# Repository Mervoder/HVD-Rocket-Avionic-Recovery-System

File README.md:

# HVD-Rocket-Avionic-Recovery-System
Rocket Main and Apogee Avionic Recovery System

1.5 ADANA WOF takımında takım arkadaşım MEHMET ALİ AĞIRMAN ile geliştirmiş olduğumuz Roket kurtarma sistemidir. 

Sistemde 2 adet açılma mevcuttur.

Kullanılan malzemeler :
MPU-6050
STM32F072
LoRa e32 433t30d
MS5611
Quectel L86 GPS

Tamamen örnek teşkil etmesi için yayımlanmıştır. İlgili kodlamalar ve detaylı bilgiler için iletişime geçebilirsiniz. 

OĞUZ KAAN ATAY
atay.oguzkaan@gmail.com

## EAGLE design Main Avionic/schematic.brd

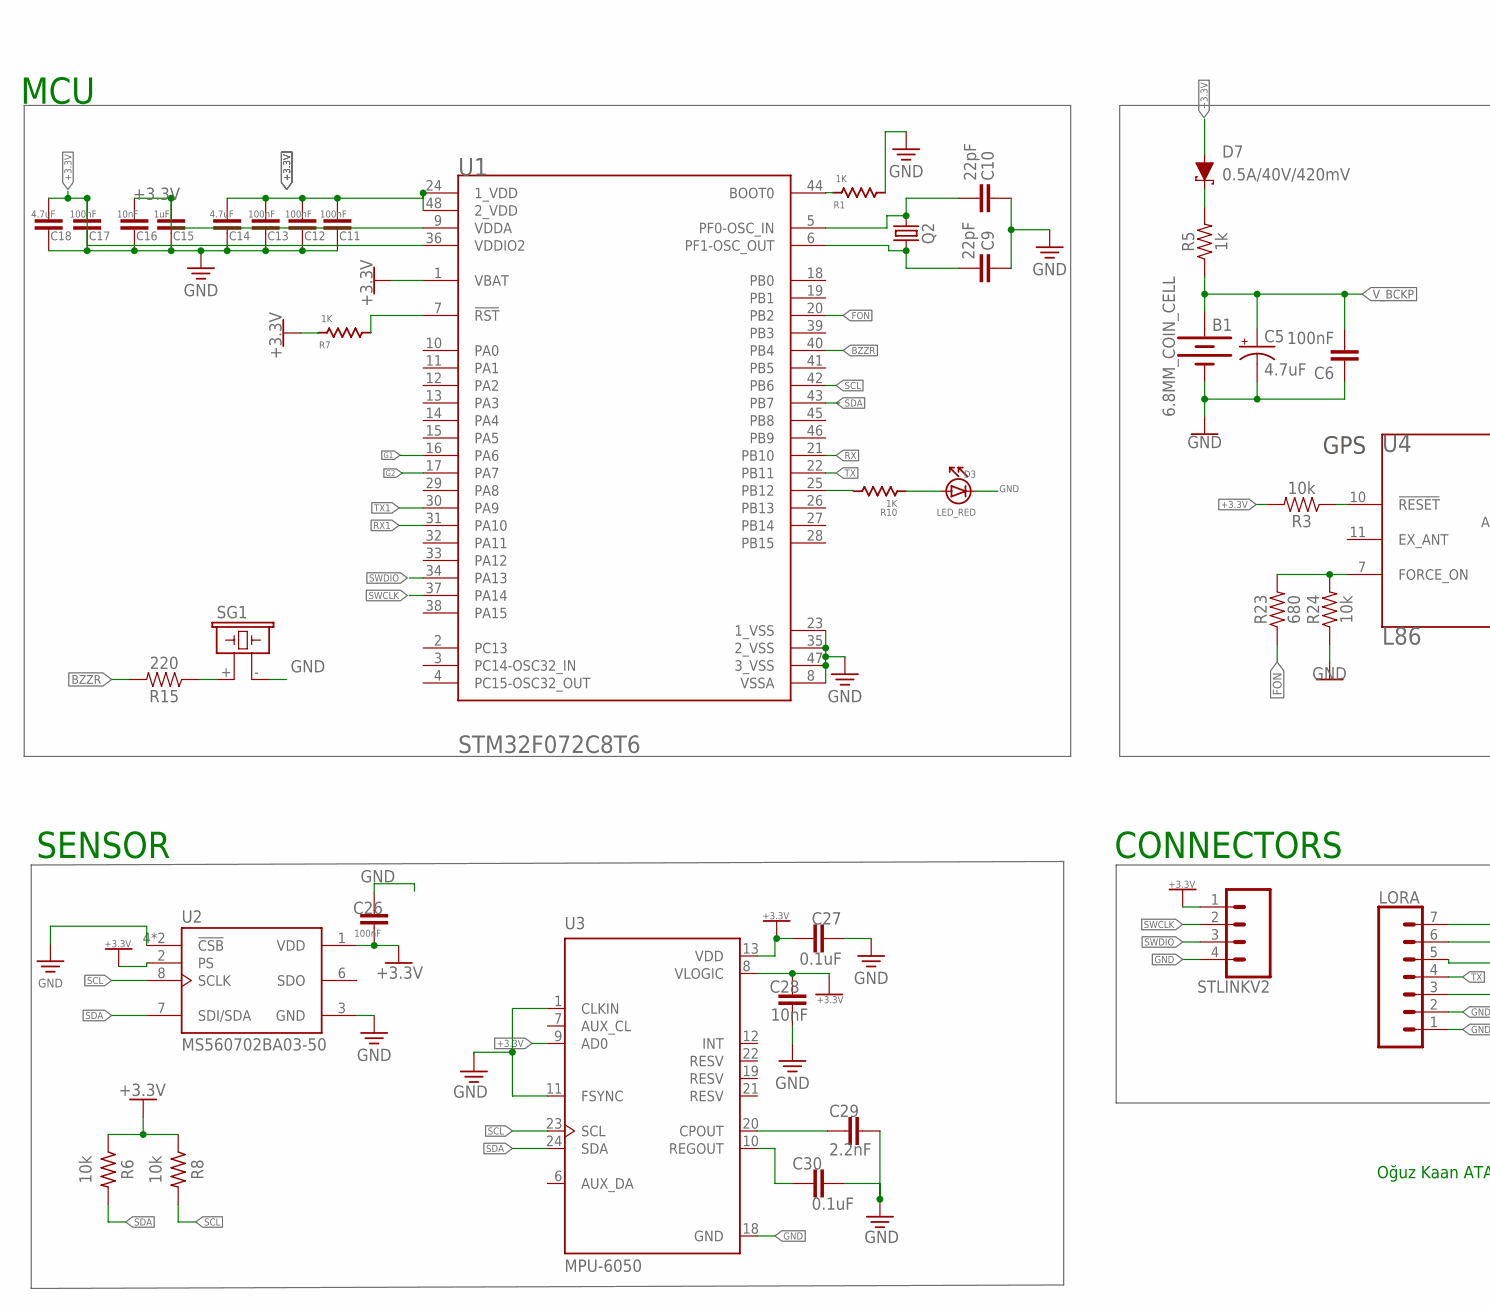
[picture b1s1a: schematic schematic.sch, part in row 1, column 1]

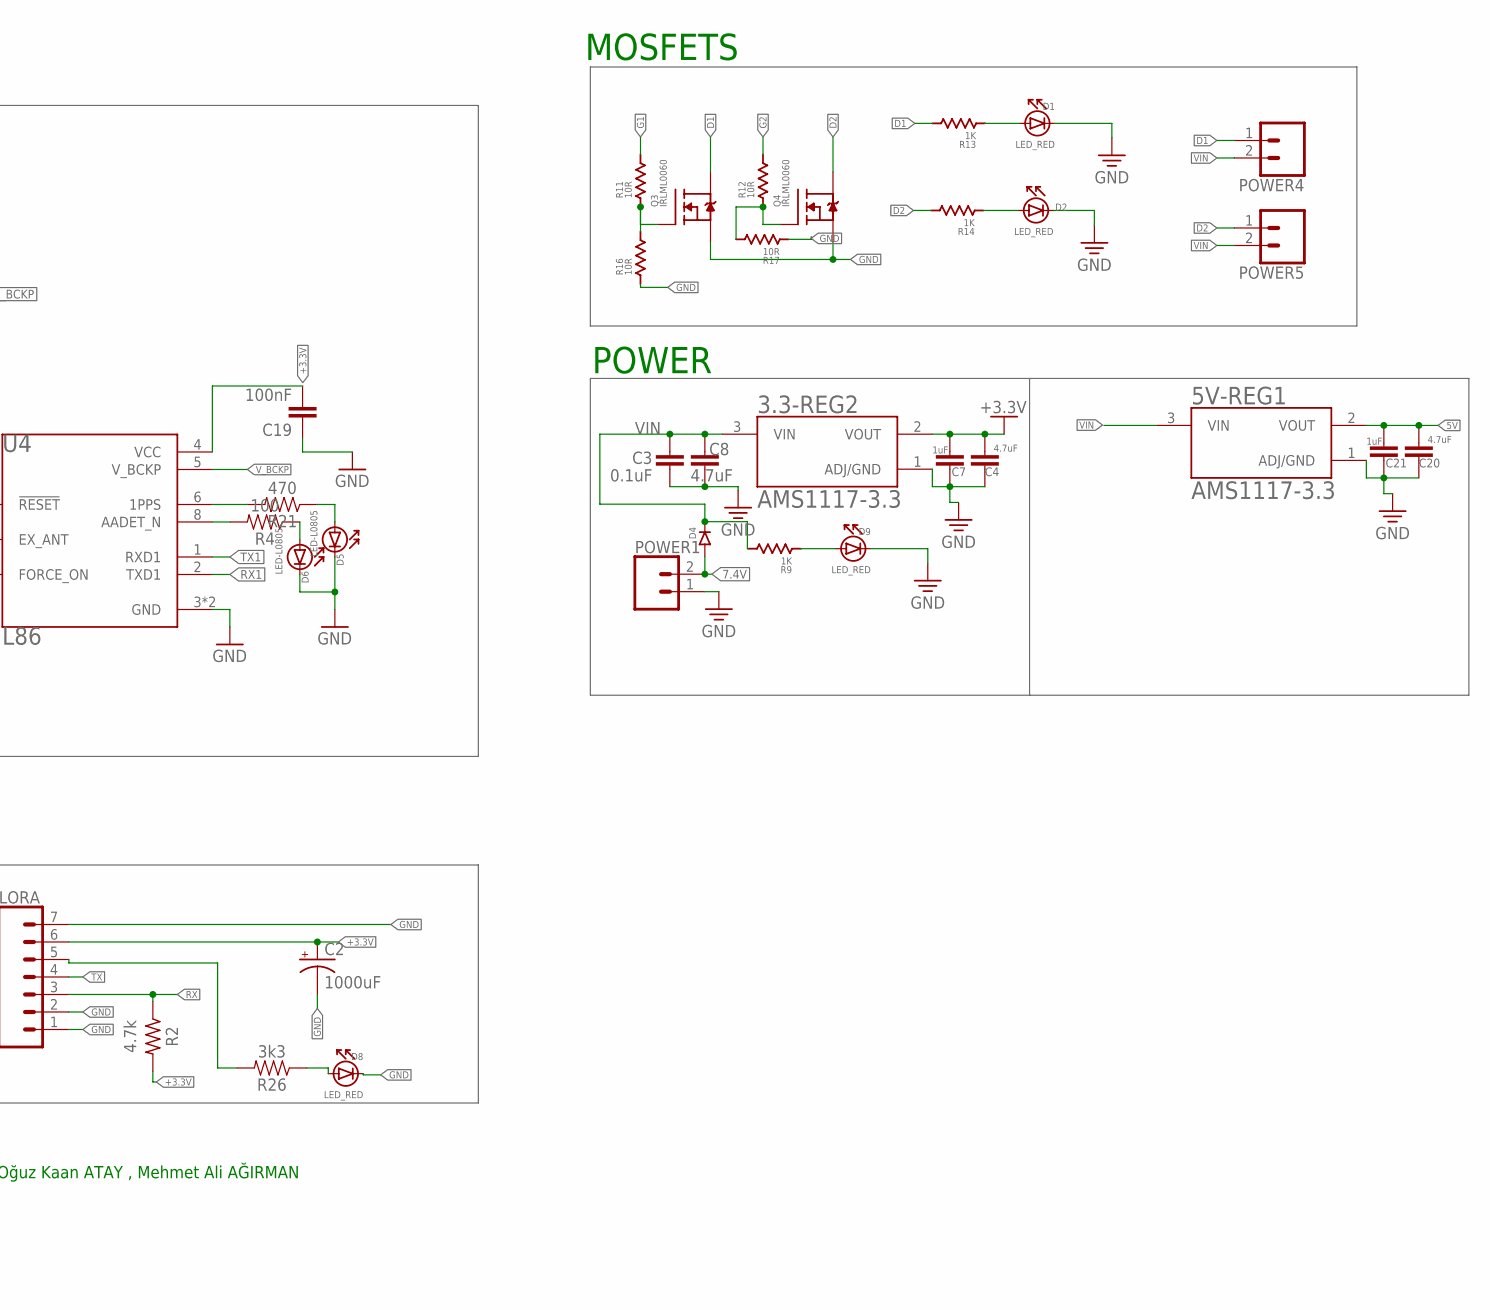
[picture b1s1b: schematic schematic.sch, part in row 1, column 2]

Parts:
3.3-REG2, 5V-REG1: AMS1117-3.3; SOT229P700X180-4N
B1: 6.8MM_COIN_CELL; BATTCON-6.8MM
C2: 1000uF; 150CLZ-1010
C3, C27, C30: 0.1uF; CAPC1608X85
C4, C8, C14, C18, C20: 4.7uF; CAPC1608X85
C5: 4.7uF; EIA3216
C6, C19: 100nF; 0603
C7, C15, C21: 1uF; CAPC1608X85
C9, C10: 22pF; CAPC1608X85
C11, C12, C13, C17, C26: 100nF; CAPC1608X85
C16, C28: 10nF; CAPC1608X85
C29: 2.2nF; CAPC1608X85
D1, D2, D3, D8, D9: LED_RED; LED_0805
D4: DIODE-SS14-DO214AC; DO-214AC
D5, D6: LED-L0805; LED_0805
D7: 0.5A/40V/420mV; SOD-323
LORA: CONN_07; 1X07
POWER1, POWER4, POWER5: CONN_023.5MM-NO_SILK; SCREWTERMINAL-3.5MM-2-NS
Q2: CRYSTALHC49U70; HC49U70
Q3, Q4: IRLML0060; SOT-23
R1, R7, R9, R10, R13, R14: 1K; RES_0805
R2: 4.7k; RESC2012X65
R3, R24: 10k; 0603
R4: 100; 0603
R5: 1k; 0603
R6, R8: 10k; RESC2012X65
R11, R12, R16, R17: 10R; RES_0805
R15: 220; 0603
R21: 470; 0603
R23: 680; 0603
R26: 3k3; 0603
SG1: F/CM12P
STLINKV2: CONN_04; 1X04
U1: STMICROELECTRONICS_STM32F072C8T6STMICROELECTRONIC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; STMICROELECTRONICS_STM32F072C8T6_0
U2: MS560702BA03-50; SON125P300X500X100-8N
U3: MPU-6050; QFN50P400X400X95-24N
U4: L86; XCVR_L86

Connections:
5V: 5V-REG1.2 (VOUT), C20.1, C21.1
7.4V: D4.A (ANOT), POWER1.2
+3.3V: 3.3-REG2.2 (VOUT), C2.+, C4.1, C7.1, C11.1, C12.1, C13.1, C14.1, C15.1, C16.1, C17.1, C18.1, C19.2, C26.1, C27.2, C28.2, D7.A, LORA.6, R2.2, R3.2, R6.1, R7.B, R8.1, STLINKV2.1, U1.1 (VBAT), U1.9 (VDDA), U1.24 (1_VDD), U1.36 (VDDIO2), U1.48 (2_VDD), U2.1 (VDD), U2.2 (PS), U3.8 (VLOGIC), U3.9 (AD0), U3.13 (VDD), U4.4 (VCC)
AUX: LORA.5, R26.2
BZZR: R15.2, U1.40 (PB4)
D1: POWER4.1, Q3.3 (D), R13.B
D2: POWER5.1, Q4.3 (D), R14.B
FON: R23.1, U1.20 (PB2)
G1: R11.B, U1.16 (PA6)
G2: R12.B, U1.17 (PA7)
GND: 3.3-REG2.1 (ADJ/GND), 5V-REG1.1 (ADJ/GND), B1.-, C2.-, C3.1, C4.2, C5.-, C6.1, C7.2, C8.1, C9.2, C10.2, C11.2, C12.2, C13.2, C14.2, C15.2, C16.2, C17.2, C18.2, C19.1, C20.2, C21.2, C26.2, C27.1, C28.1, C29.1, C30.1, D1.K (KATOT), D2.K (KATOT), D3.K (KATOT), D5.K (KATOT), D6.K (KATOT), D8.K (KATOT), D9.K (KATOT), LORA.1, LORA.2, LORA.7, POWER1.1, Q3.2 (S), Q4.2 (S), R1.A, R16.A, R17.A, R24.1, SG1.- (2), STLINKV2.4, U1.8 (VSSA), U1.23 (1_VSS), U1.35 (2_VSS), U1.47 (3_VSS), U2.3 (GND), U2.4 (!CSB), U2.5 (!CSB), U3.1 (CLKIN), U3.11 (FSYNC), U3.18 (GND), U4.3 (GND), U4.12 (GND)
unnamed: R3.1, U4.10 (!RESET)
unnamed: R4.2, U4.8 (AADET_N)
unnamed: D6.A (ANOT), R4.1
unnamed: D7.C, R5.2
unnamed: R1.B, U1.44 (BOOT0)
unnamed: C29.2, U3.20 (CPOUT)
unnamed: C30.2, U3.10 (REGOUT)
unnamed: D9.A (ANOT), R9.A
unnamed: R7.A, U1.7 (!RST!)
unnamed: D3.A (ANOT), R10.A
unnamed: Q3.1 (G), R11.A, R16.B
unnamed: R21.2, U4.6 (1PPS)
unnamed: D5.A (ANOT), R21.1
unnamed: R15.1, SG1.+ (1)
unnamed: Q4.1 (G), R12.A, R17.B
unnamed: D2.A (ANOT), R14.A
unnamed: D1.A (ANOT), R13.A
unnamed: R10.B, U1.25 (PB12)
unnamed: D8.A (ANOT), R26.1
unnamed: R23.2, R24.2, U4.7 (FORCE_ON)
RX: LORA.3, R2.1, U1.21 (PB10)
RX1: U1.31 (PA10), U4.2 (TXD1)
SCL: R8.2, U1.42 (PB6), U2.8 (SCLK), U3.23 (SCL)
SDA: R6.2, U1.43 (PB7), U2.7 (SDI/SDA), U3.24 (SDA)
SWCLK: STLINKV2.2, U1.37 (PA14)
SWDIO: STLINKV2.3, U1.34 (PA13)
TX: LORA.4, U1.22 (PB11)
TX1: U1.30 (PA9), U4.1 (RXD1)
VIN: 3.3-REG2.3 (VIN), 5V-REG1.3 (VIN), C3.2, C8.2, D4.K (KATOT), POWER4.2, POWER5.2, R9.B
V_BCKP: B1.+, C5.+, C6.2, R5.1, U4.5 (V_BCKP)
XTAL1: C10.1, Q2.1, U1.5 (PF0-OSC_IN)
XTAL2: C9.1, Q2.2, U1.6 (PF1-OSC_OUT)

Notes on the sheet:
POWER
SENSOR
MCU
Oğuz Kaan ATAY , Mehmet Ali AĞIRMAN
CONNECTORS
MOSFETS
GPS

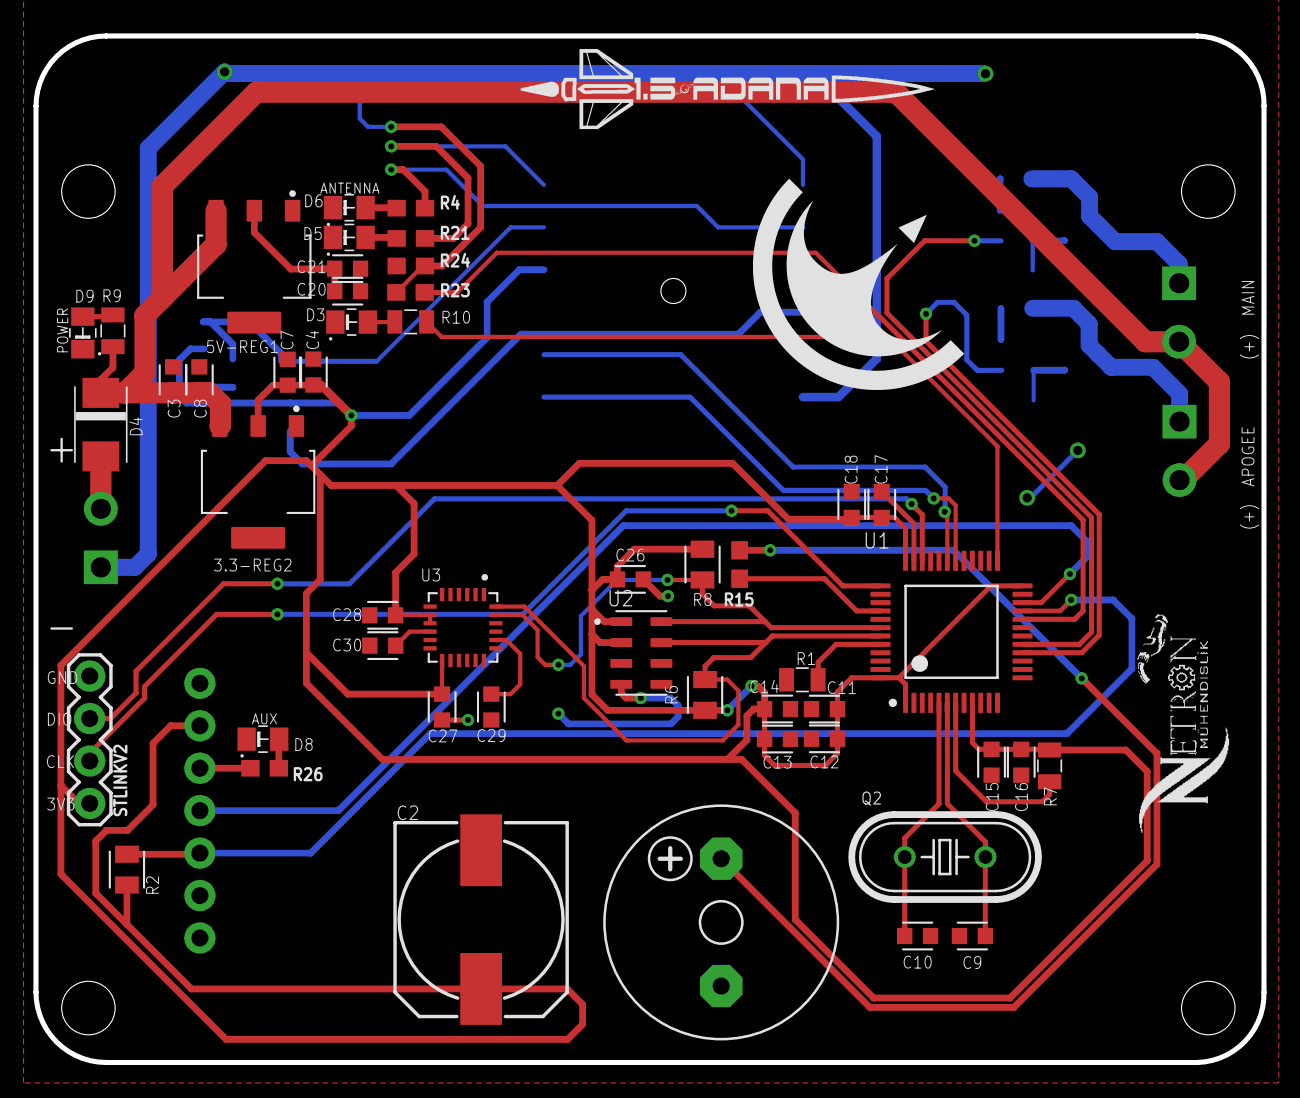
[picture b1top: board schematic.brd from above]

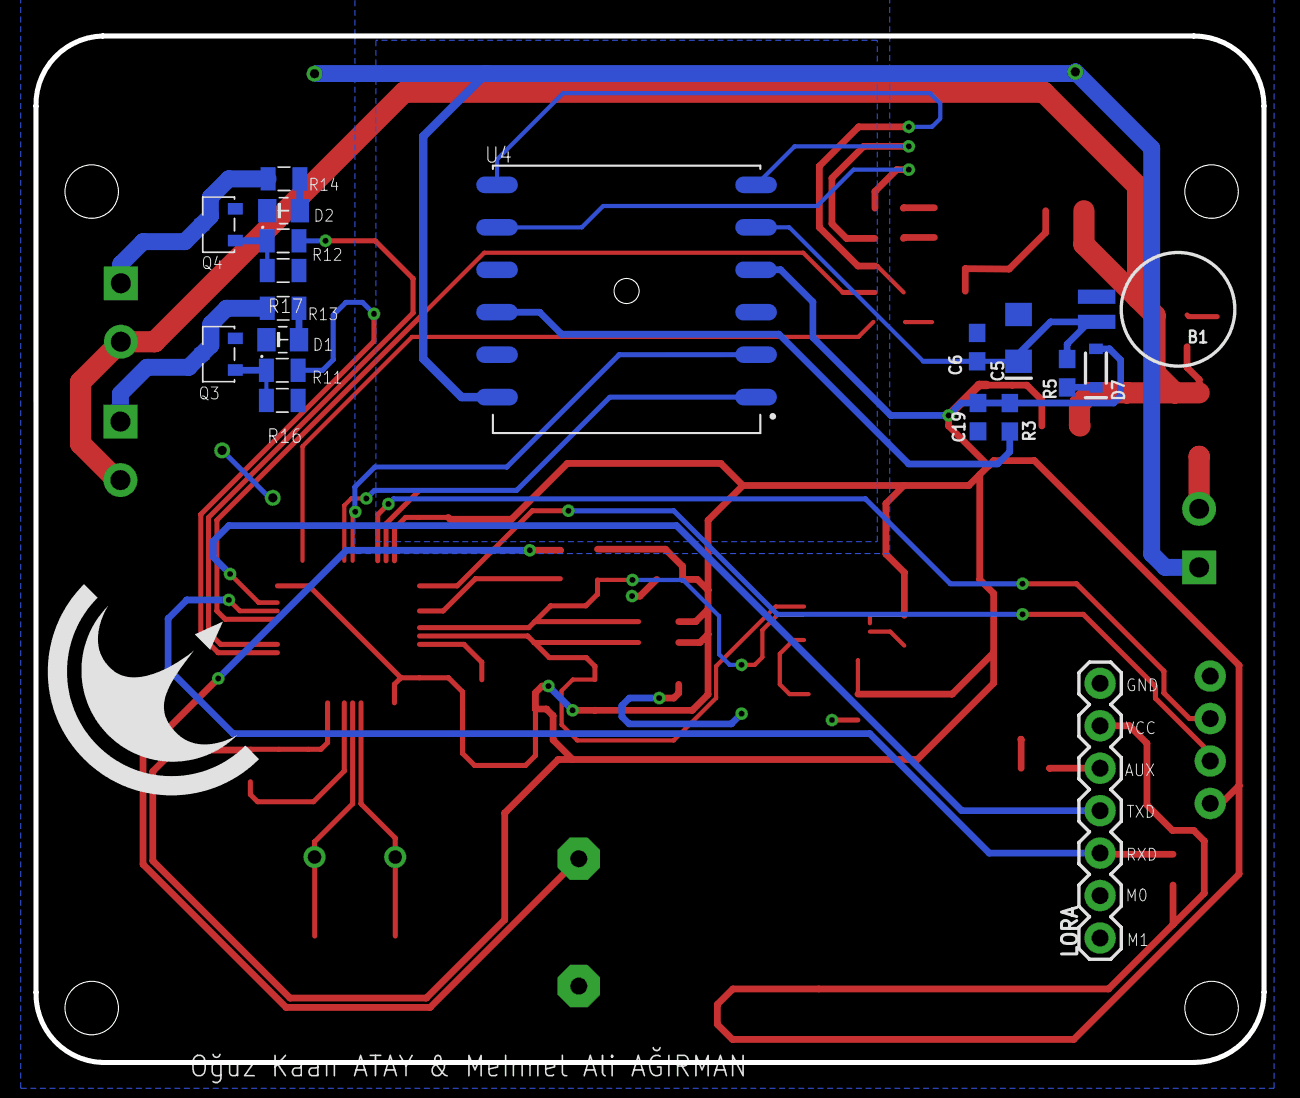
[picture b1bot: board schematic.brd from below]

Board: 2 copper layers, 73.5 x 61.4 mm, 71 parts (19 on the bottom side), 43 nets.

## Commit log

2022-08-15 Rocket Avionic Recovery System
    1.5 Adana WOF takımında takım arkadaşım Mehmet Ali AĞIRMAN ile birlikte geliştirmiş olduğumuz model roket kurtarma sistemimizdir. Sistem 2 açılma yapabilmektedir.
    Kullanılan malzemeler ;
    Stm32F072
    MS5611
    LoRa E32 433T30D
    Quectel GPS
2022-08-15 README.md
2022-08-15 Pictures

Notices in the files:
parts and their libraries:
SparkFun-Connectors: Licensing: Creative Commons ShareAlike 4.0 International - https://creativecommons.org/licenses/by-sa/4.0
